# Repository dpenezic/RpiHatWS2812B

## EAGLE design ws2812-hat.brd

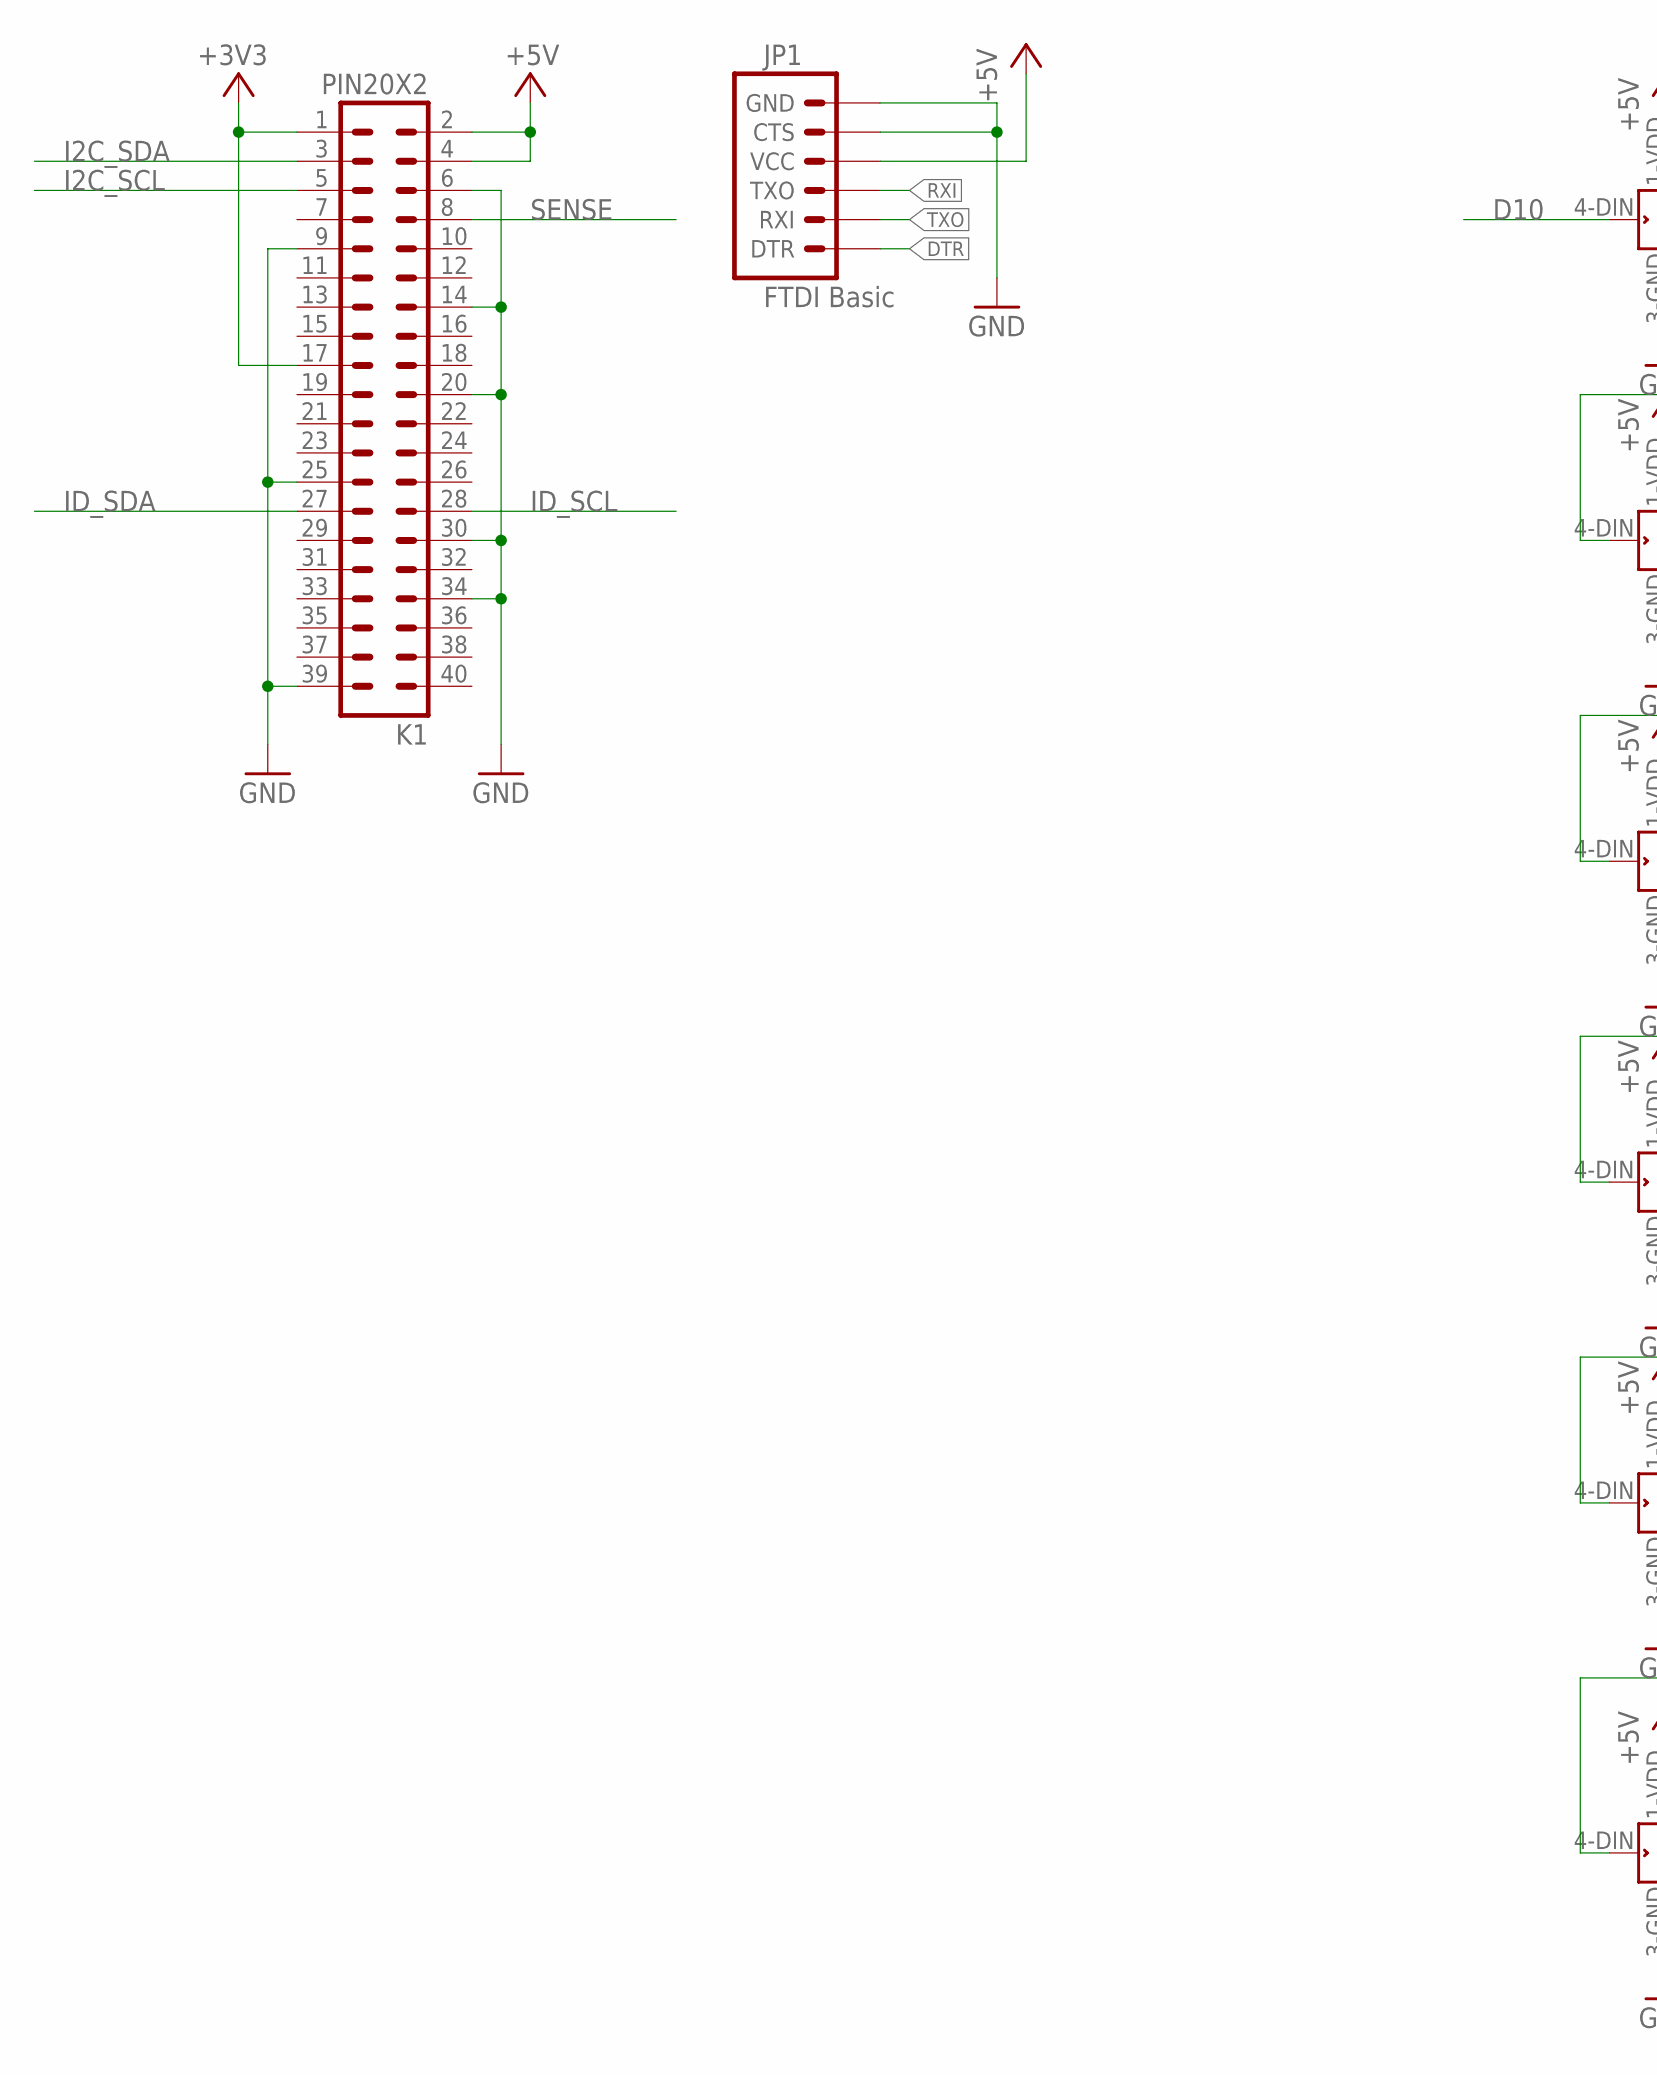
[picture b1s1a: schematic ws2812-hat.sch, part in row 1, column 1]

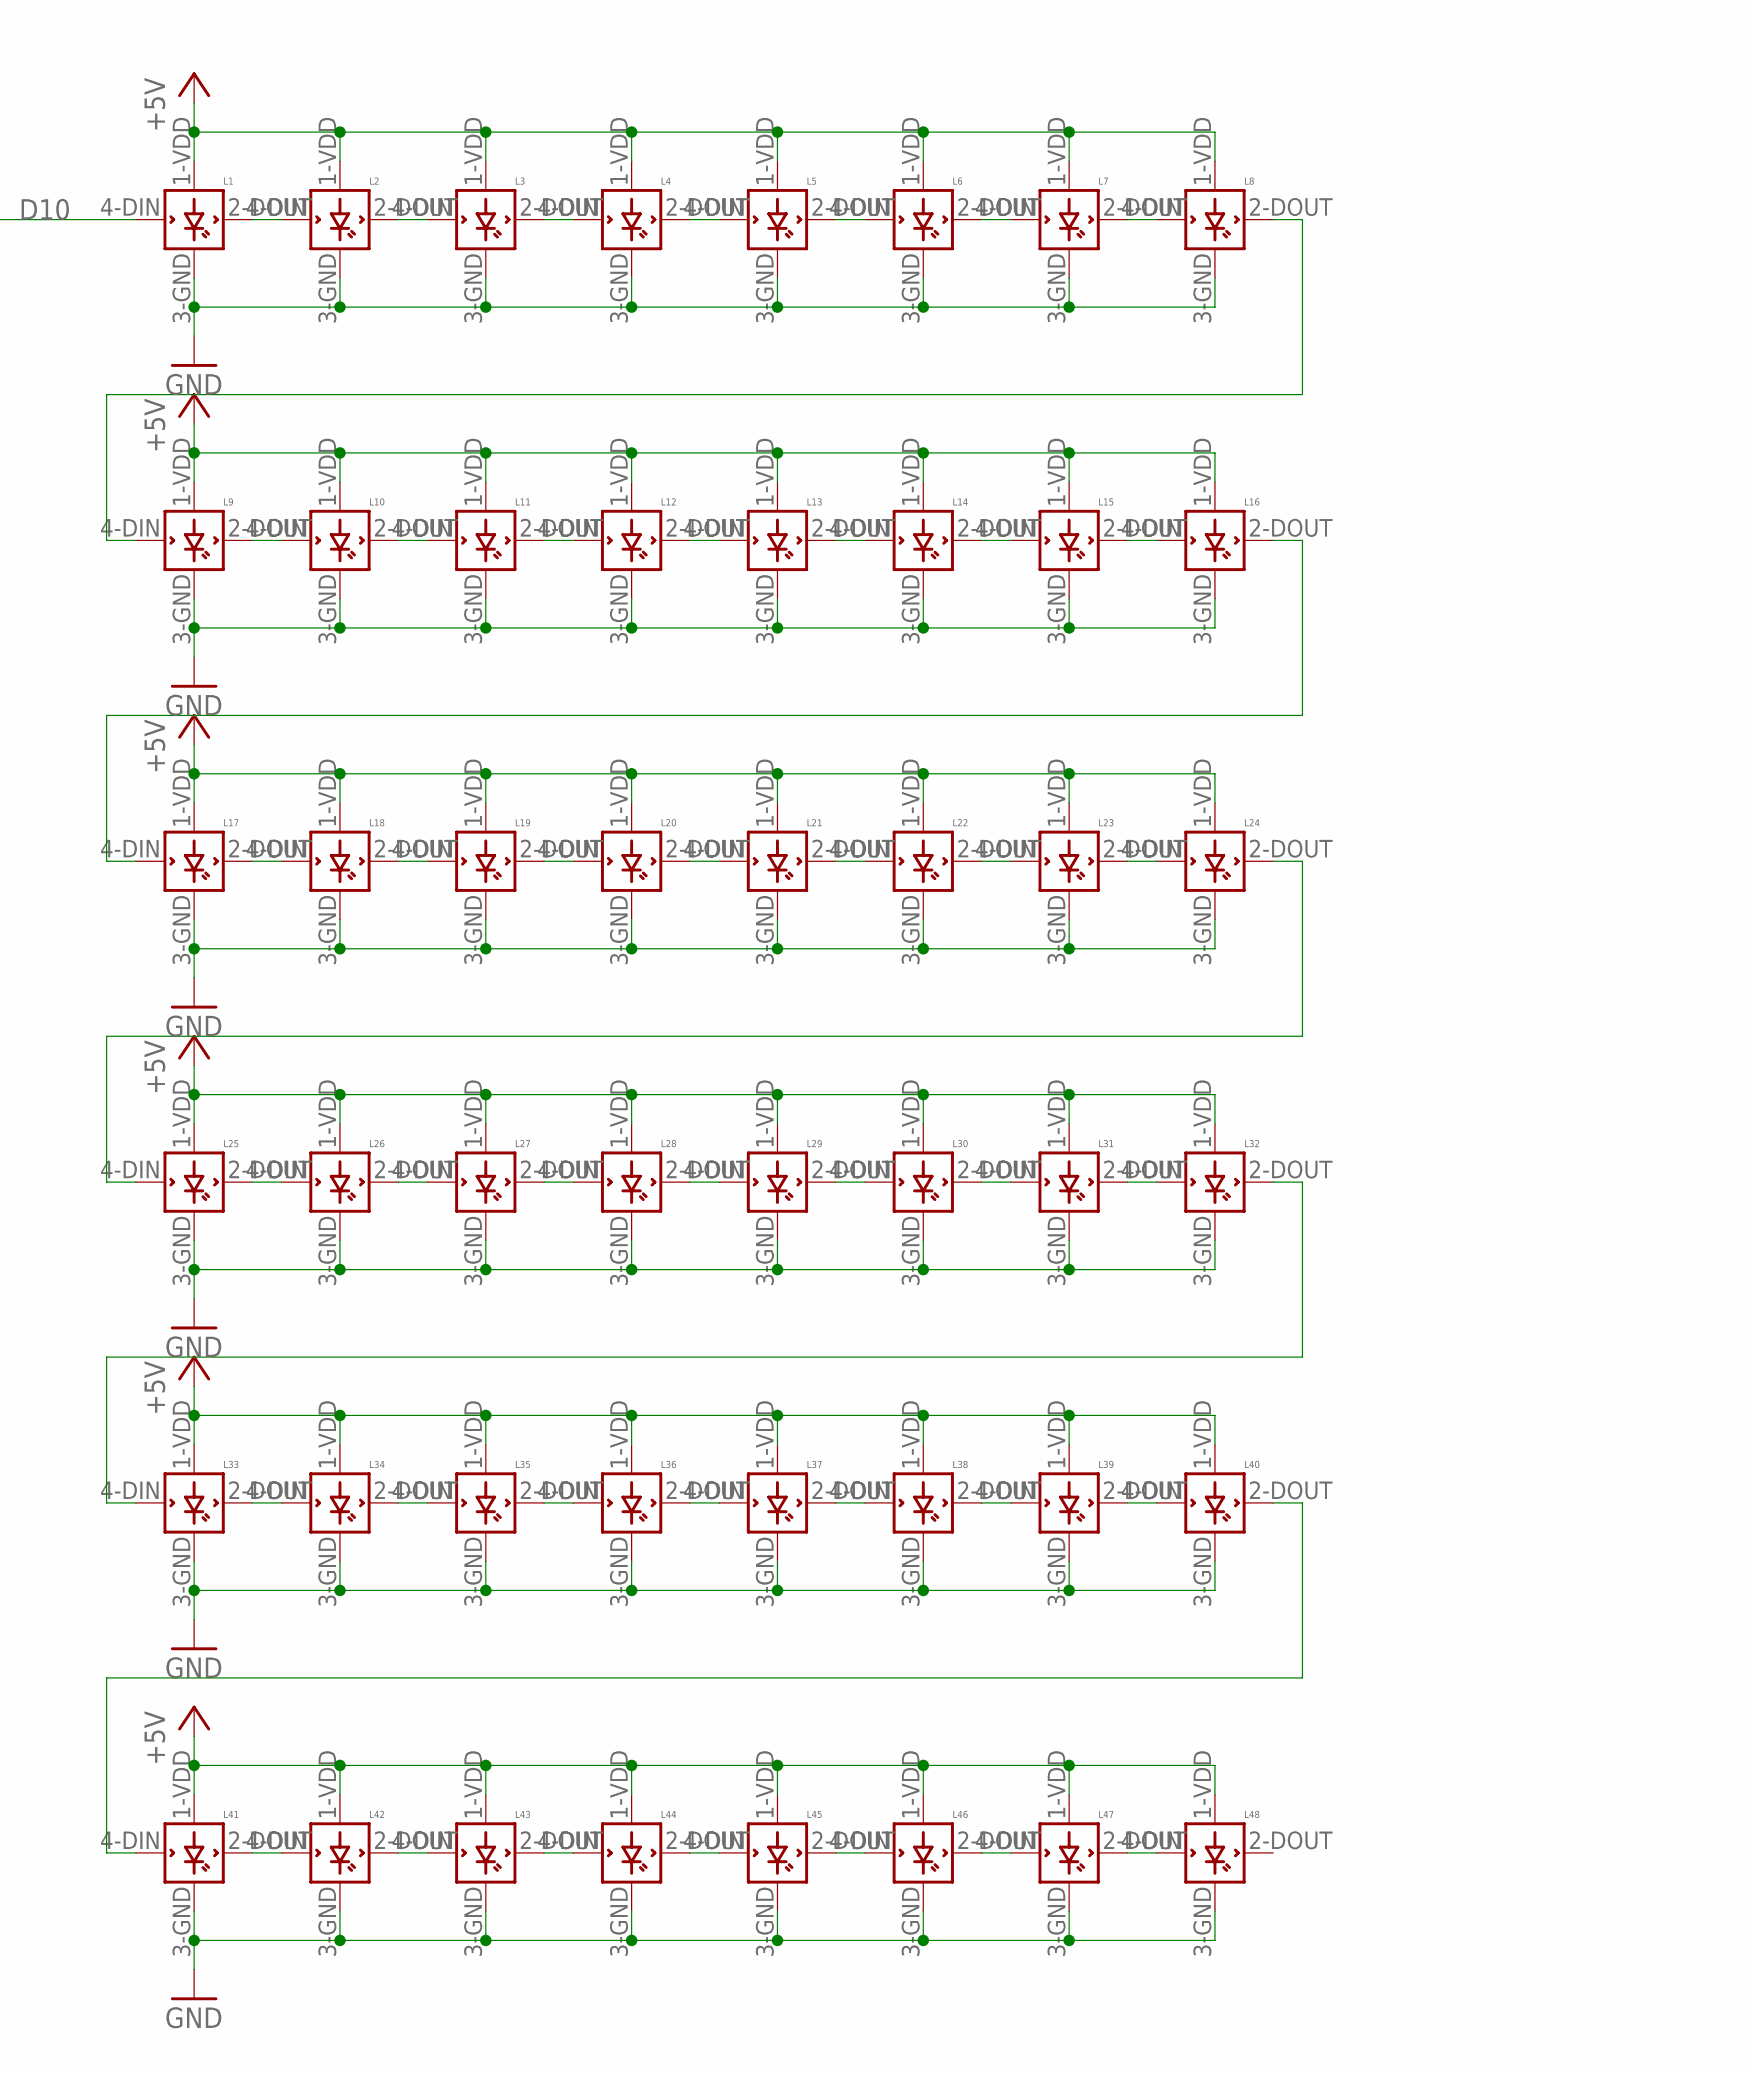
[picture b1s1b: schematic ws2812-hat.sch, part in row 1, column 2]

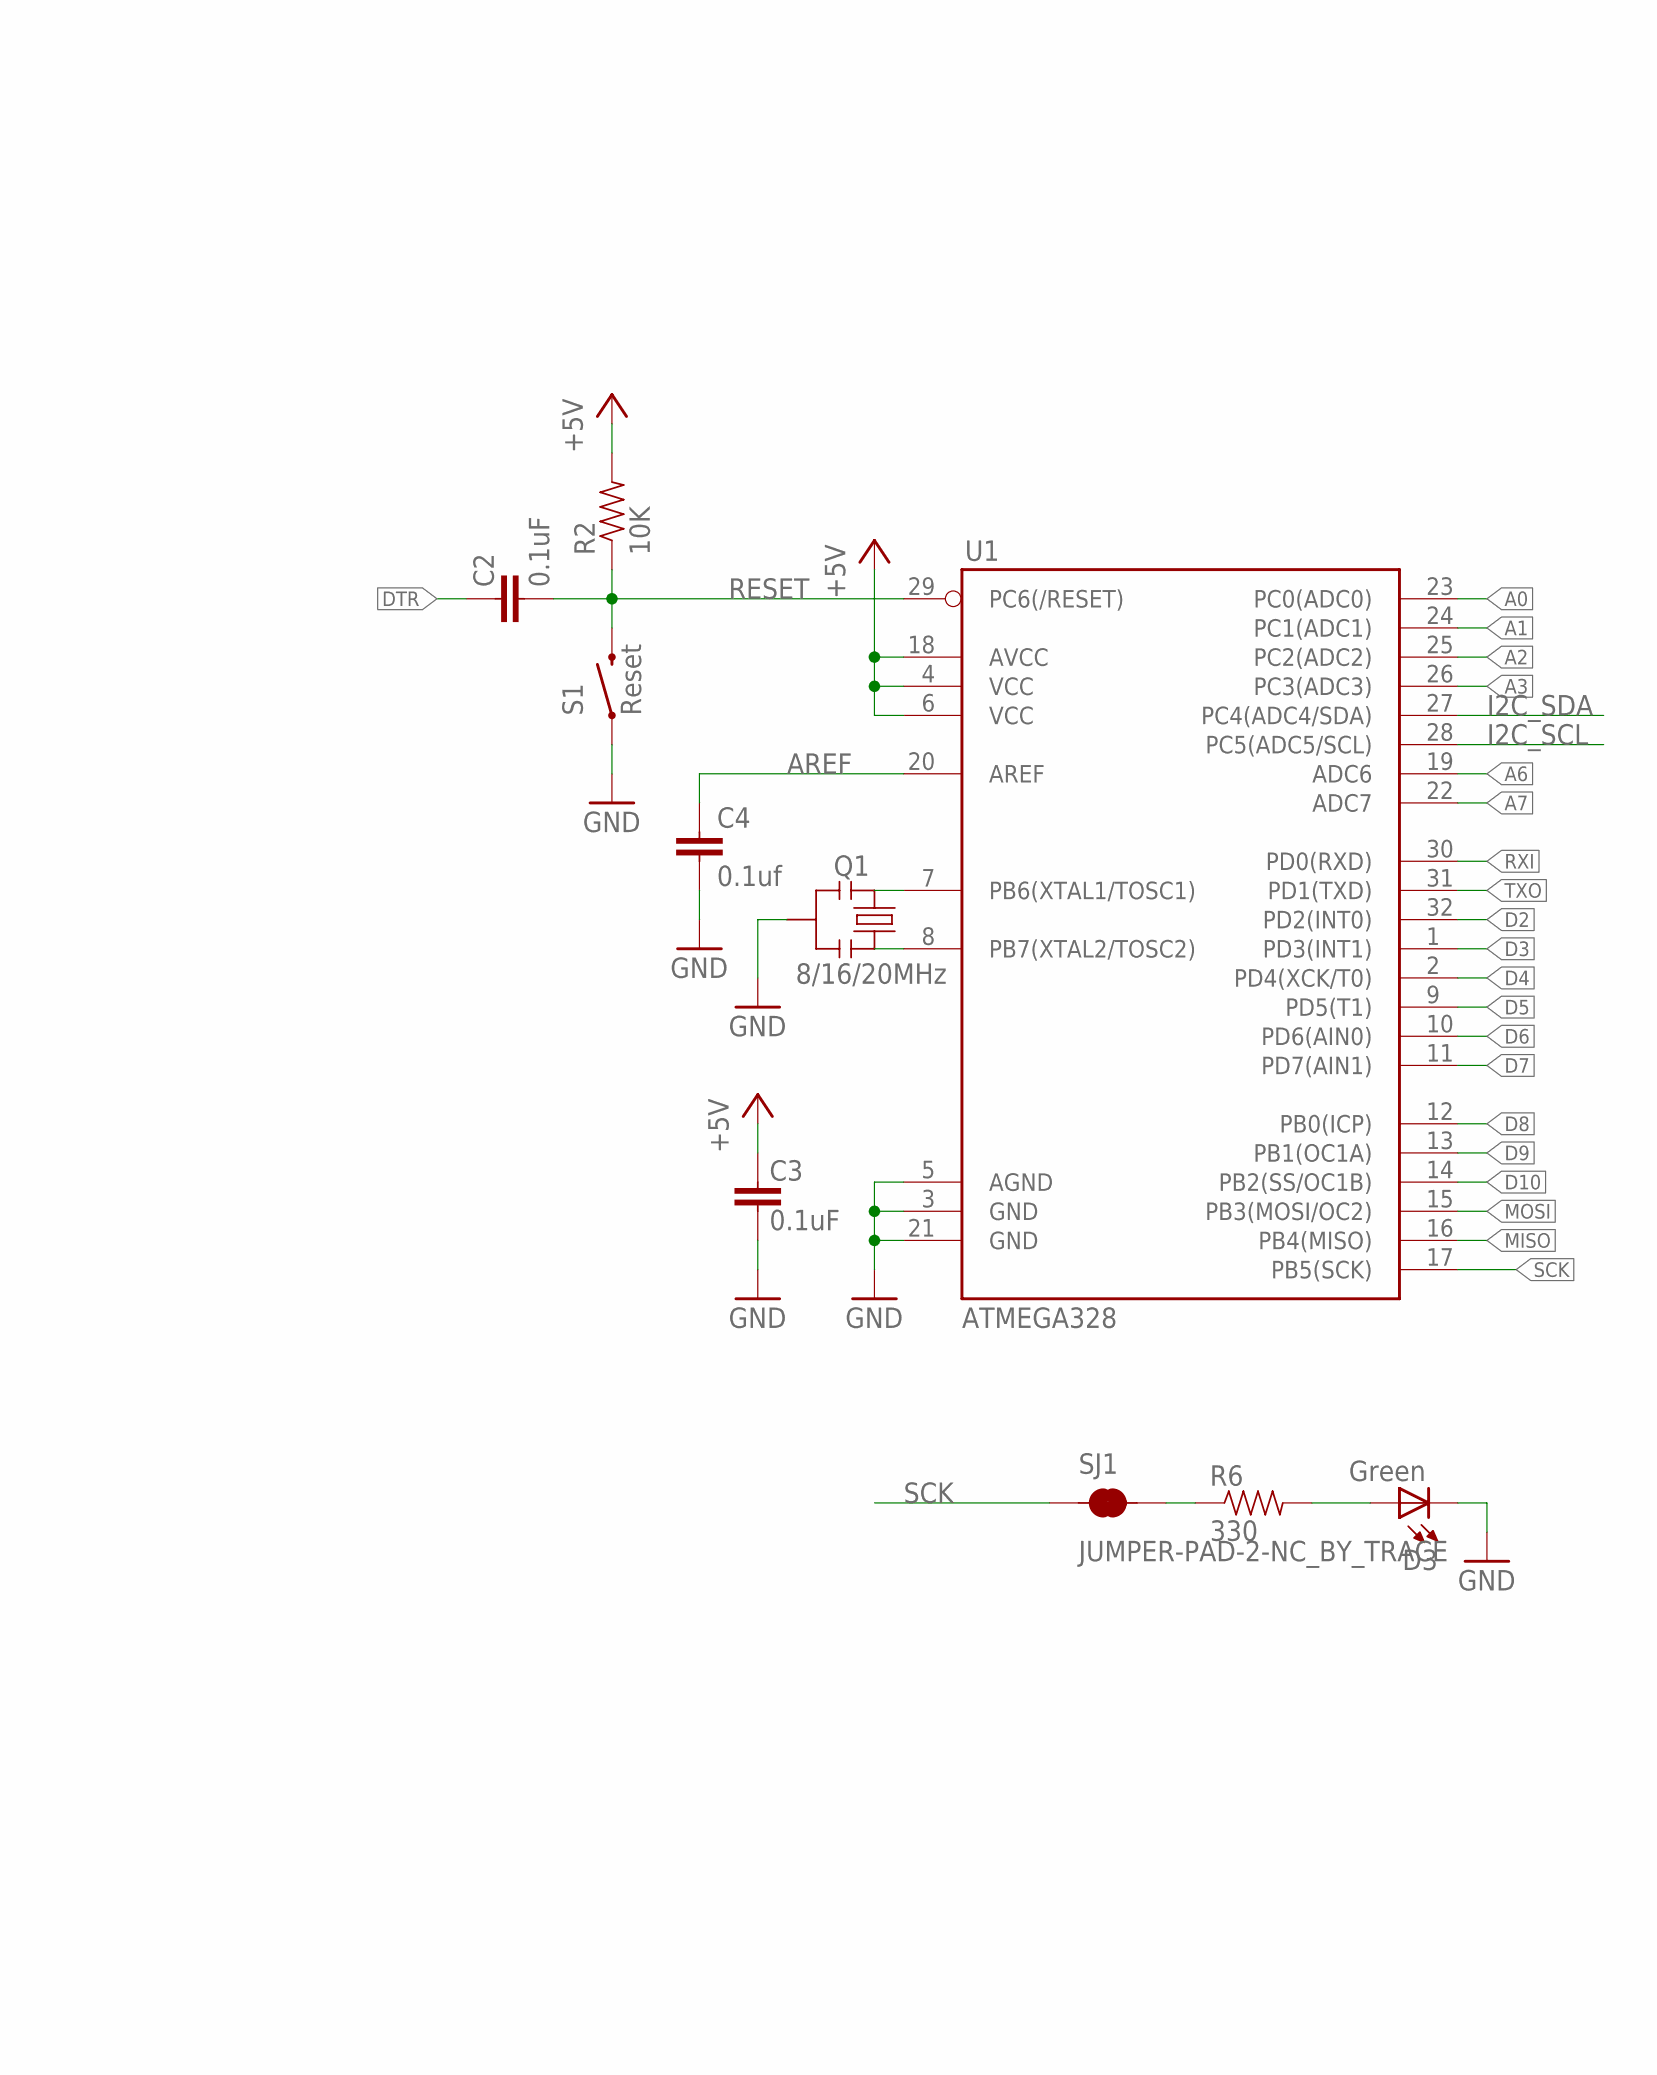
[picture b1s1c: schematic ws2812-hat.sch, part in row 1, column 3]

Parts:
C2, C3: 0.1uF; 0603-CAP
C4: 0.1uf; C0805K
D3: Green; 0603-LED-ALT1
JP1: FTDI Basic; 1X06
K1: PIN20X2; PIN_20X2
L1, L2, L3, L4, L5, L6, L7, L8, L9, L10, L11, L12, L13, L14, L15, L16, L17, L18, L19, L20, L21, L22, L23, L24, L25, L26, L27, L28, L29, L30, L31, L32, L33, L34, L35, L36, L37, L38, L39, L40, L41, L42, L43, L44, L45, L46, L47, L48: WS2812B
Q1: 8/16/20MHz; RESONATOR-SMD-1:1
R2: 10K; 0603-RES
R6: 330; 0603-RES
S1: Reset; TACTILE-SWITCH-SMD-ALT01
SJ1: JUMPER-PAD-2-NC_BY_TRACE; PAD-JUMPER-2-NC_BY_TRACE_YES_SILK
U1: ATMEGA328; TQFP32-08

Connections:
+3V3: K1.1, K1.17
+5V: C3.2, JP1.4 (VCC), K1.2, K1.4, L1.1-VDD (VDD), L2.1-VDD (VDD), L3.1-VDD (VDD), L4.1-VDD (VDD), L5.1-VDD (VDD), L6.1-VDD (VDD), L7.1-VDD (VDD), L8.1-VDD (VDD), L9.1-VDD (VDD), L10.1-VDD (VDD), L11.1-VDD (VDD), L12.1-VDD (VDD), L13.1-VDD (VDD), L14.1-VDD (VDD), L15.1-VDD (VDD), L16.1-VDD (VDD), L17.1-VDD (VDD), L18.1-VDD (VDD), L19.1-VDD (VDD), L20.1-VDD (VDD), L21.1-VDD (VDD), L22.1-VDD (VDD), L23.1-VDD (VDD), L24.1-VDD (VDD), L25.1-VDD (VDD), L26.1-VDD (VDD), L27.1-VDD (VDD), L28.1-VDD (VDD), L29.1-VDD (VDD), L30.1-VDD (VDD), L31.1-VDD (VDD), L32.1-VDD (VDD), L33.1-VDD (VDD), L34.1-VDD (VDD), L35.1-VDD (VDD), L36.1-VDD (VDD), L37.1-VDD (VDD), L38.1-VDD (VDD), L39.1-VDD (VDD), L40.1-VDD (VDD), L41.1-VDD (VDD), L42.1-VDD (VDD), L43.1-VDD (VDD), L44.1-VDD (VDD), L45.1-VDD (VDD), L46.1-VDD (VDD), L47.1-VDD (VDD), L48.1-VDD (VDD), R2.2, U1.4 (VCC), U1.6 (VCC), U1.18 (AVCC)
A0: U1.23 (PC0(ADC0))
A1: U1.24 (PC1(ADC1))
A2: U1.25 (PC2(ADC2))
A3: U1.26 (PC3(ADC3))
A6: U1.19 (ADC6)
A7: U1.22 (ADC7)
AREF: C4.1, U1.20 (AREF)
D2: U1.32 (PD2(INT0))
D3: U1.1 (PD3(INT1))
D4: U1.2 (PD4(XCK/T0))
D5: U1.9 (PD5(T1))
D6: U1.10 (PD6(AIN0))
D7: U1.11 (PD7(AIN1))
D8: U1.12 (PB0(ICP))
D9: U1.13 (PB1(OC1A))
D10: L1.4-DIN (DIN), U1.14 (PB2(SS/OC1B))
DTR: C2.2, JP1.1 (DTR)
GND: C3.1, C4.2, D3.C, JP1.5 (CTS), JP1.6 (GND), K1.6, K1.9, K1.14, K1.20, K1.25, K1.30, K1.34, K1.39, L1.3-GND (GND), L2.3-GND (GND), L3.3-GND (GND), L4.3-GND (GND), L5.3-GND (GND), L6.3-GND (GND), L7.3-GND (GND), L8.3-GND (GND), L9.3-GND (GND), L10.3-GND (GND), L11.3-GND (GND), L12.3-GND (GND), L13.3-GND (GND), L14.3-GND (GND), L15.3-GND (GND), L16.3-GND (GND), L17.3-GND (GND), L18.3-GND (GND), L19.3-GND (GND), L20.3-GND (GND), L21.3-GND (GND), L22.3-GND (GND), L23.3-GND (GND), L24.3-GND (GND), L25.3-GND (GND), L26.3-GND (GND), L27.3-GND (GND), L28.3-GND (GND), L29.3-GND (GND), L30.3-GND (GND), L31.3-GND (GND), L32.3-GND (GND), L33.3-GND (GND), L34.3-GND (GND), L35.3-GND (GND), L36.3-GND (GND), L37.3-GND (GND), L38.3-GND (GND), L39.3-GND (GND), L40.3-GND (GND), L41.3-GND (GND), L42.3-GND (GND), L43.3-GND (GND), L44.3-GND (GND), L45.3-GND (GND), L46.3-GND (GND), L47.3-GND (GND), L48.3-GND (GND), Q1.2, S1.1, S1.2 (1), U1.3 (GND), U1.5 (AGND), U1.21 (GND)
I2C_SCL: K1.5, U1.28 (PC5(ADC5/SCL))
I2C_SDA: K1.3, U1.27 (PC4(ADC4/SDA))
ID_SCL: K1.28
ID_SDA: K1.27
MISO: U1.16 (PB4(MISO))
MOSI: U1.15 (PB3(MOSI/OC2))
unnamed: L9.2-DOUT (DOUT), L10.4-DIN (DIN)
unnamed: L1.2-DOUT (DOUT), L2.4-DIN (DIN)
unnamed: L2.2-DOUT (DOUT), L3.4-DIN (DIN)
unnamed: L3.2-DOUT (DOUT), L4.4-DIN (DIN)
unnamed: L4.2-DOUT (DOUT), L5.4-DIN (DIN)
unnamed: L5.2-DOUT (DOUT), L6.4-DIN (DIN)
unnamed: L6.2-DOUT (DOUT), L7.4-DIN (DIN)
unnamed: L7.2-DOUT (DOUT), L8.4-DIN (DIN)
unnamed: L10.2-DOUT (DOUT), L11.4-DIN (DIN)
unnamed: L11.2-DOUT (DOUT), L12.4-DIN (DIN)
unnamed: L12.2-DOUT (DOUT), L13.4-DIN (DIN)
unnamed: L13.2-DOUT (DOUT), L14.4-DIN (DIN)
unnamed: L14.2-DOUT (DOUT), L15.4-DIN (DIN)
unnamed: L15.2-DOUT (DOUT), L16.4-DIN (DIN)
unnamed: L17.2-DOUT (DOUT), L18.4-DIN (DIN)
unnamed: L18.2-DOUT (DOUT), L19.4-DIN (DIN)
unnamed: L19.2-DOUT (DOUT), L20.4-DIN (DIN)
unnamed: L20.2-DOUT (DOUT), L21.4-DIN (DIN)
unnamed: L21.2-DOUT (DOUT), L22.4-DIN (DIN)
unnamed: L22.2-DOUT (DOUT), L23.4-DIN (DIN)
unnamed: L23.2-DOUT (DOUT), L24.4-DIN (DIN)
unnamed: L25.2-DOUT (DOUT), L26.4-DIN (DIN)
unnamed: L26.2-DOUT (DOUT), L27.4-DIN (DIN)
unnamed: L27.2-DOUT (DOUT), L28.4-DIN (DIN)
unnamed: L28.2-DOUT (DOUT), L29.4-DIN (DIN)
unnamed: L29.2-DOUT (DOUT), L30.4-DIN (DIN)
unnamed: L30.2-DOUT (DOUT), L31.4-DIN (DIN)
unnamed: L31.2-DOUT (DOUT), L32.4-DIN (DIN)
unnamed: D3.A, R6.2
unnamed: Q1.3, U1.8 (PB7(XTAL2/TOSC2))
unnamed: Q1.1, U1.7 (PB6(XTAL1/TOSC1))
unnamed: L33.2-DOUT (DOUT), L34.4-DIN (DIN)
unnamed: L34.2-DOUT (DOUT), L35.4-DIN (DIN)
unnamed: L35.2-DOUT (DOUT), L36.4-DIN (DIN)
unnamed: L36.2-DOUT (DOUT), L37.4-DIN (DIN)
unnamed: L37.2-DOUT (DOUT), L38.4-DIN (DIN)
unnamed: L38.2-DOUT (DOUT), L39.4-DIN (DIN)
unnamed: L39.2-DOUT (DOUT), L40.4-DIN (DIN)
unnamed: L41.2-DOUT (DOUT), L42.4-DIN (DIN)
unnamed: L42.2-DOUT (DOUT), L43.4-DIN (DIN)
unnamed: L43.2-DOUT (DOUT), L44.4-DIN (DIN)
unnamed: L44.2-DOUT (DOUT), L45.4-DIN (DIN)
unnamed: L45.2-DOUT (DOUT), L46.4-DIN (DIN)
unnamed: L46.2-DOUT (DOUT), L47.4-DIN (DIN)
unnamed: L47.2-DOUT (DOUT), L48.4-DIN (DIN)
unnamed: L8.2-DOUT (DOUT), L9.4-DIN (DIN)
unnamed: L16.2-DOUT (DOUT), L17.4-DIN (DIN)
unnamed: L24.2-DOUT (DOUT), L25.4-DIN (DIN)
unnamed: L40.2-DOUT (DOUT), L41.4-DIN (DIN)
unnamed: L32.2-DOUT (DOUT), L33.4-DIN (DIN)
unnamed: R6.1, SJ1.2
RESET: C2.1, R2.1, S1.3 (2), S1.4 (2), U1.29 (PC6(/RESET))
RXI: JP1.3 (TXO), U1.30 (PD0(RXD))
SCK: SJ1.1, U1.17 (PB5(SCK))
SENSE: K1.8
TXO: JP1.2 (RXI), U1.31 (PD1(TXD))

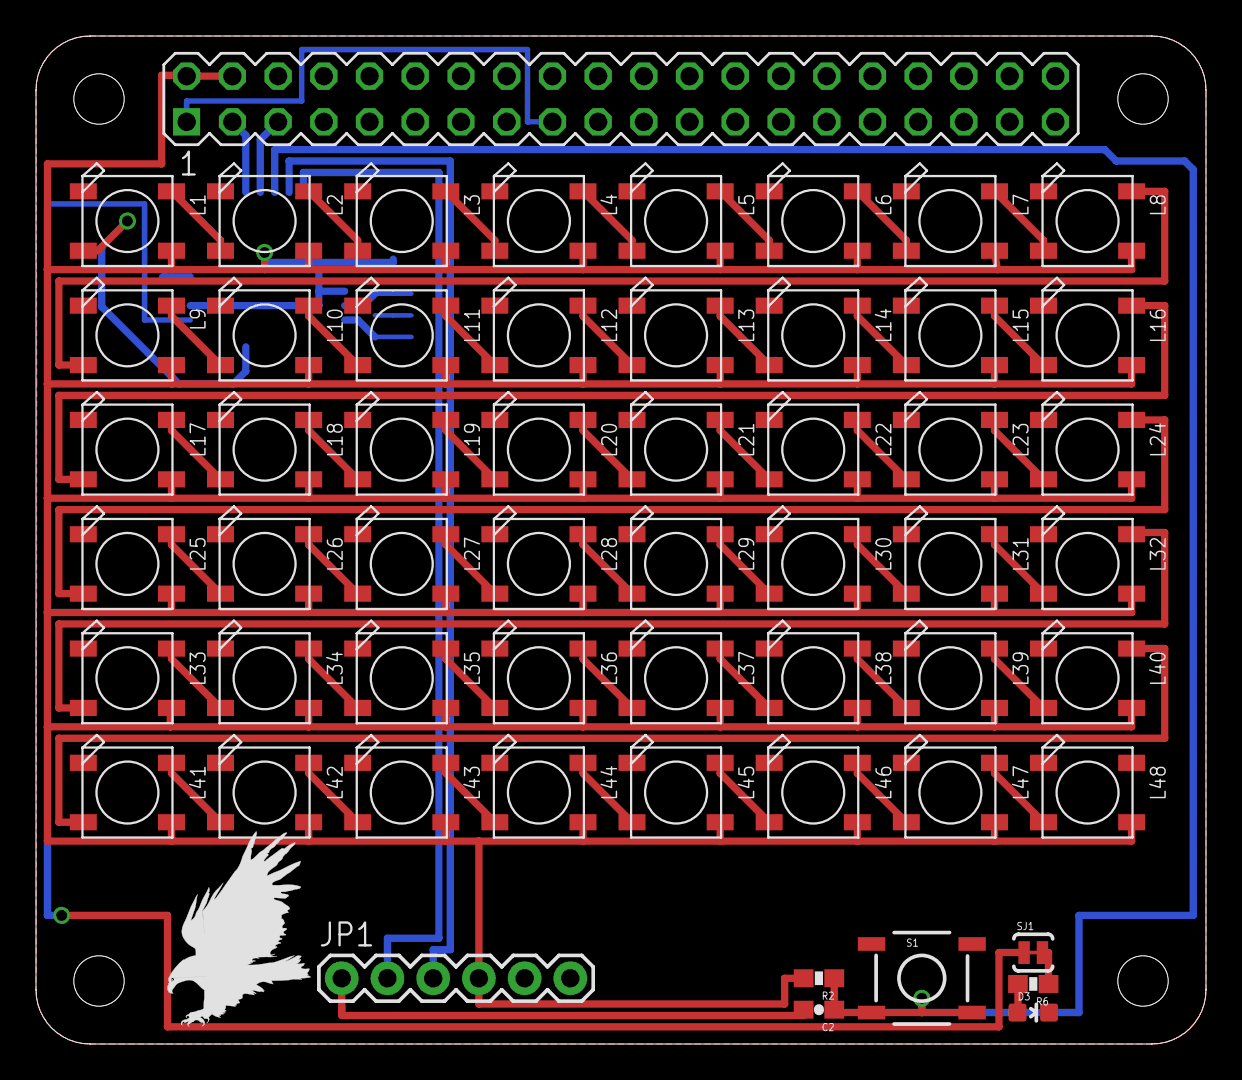
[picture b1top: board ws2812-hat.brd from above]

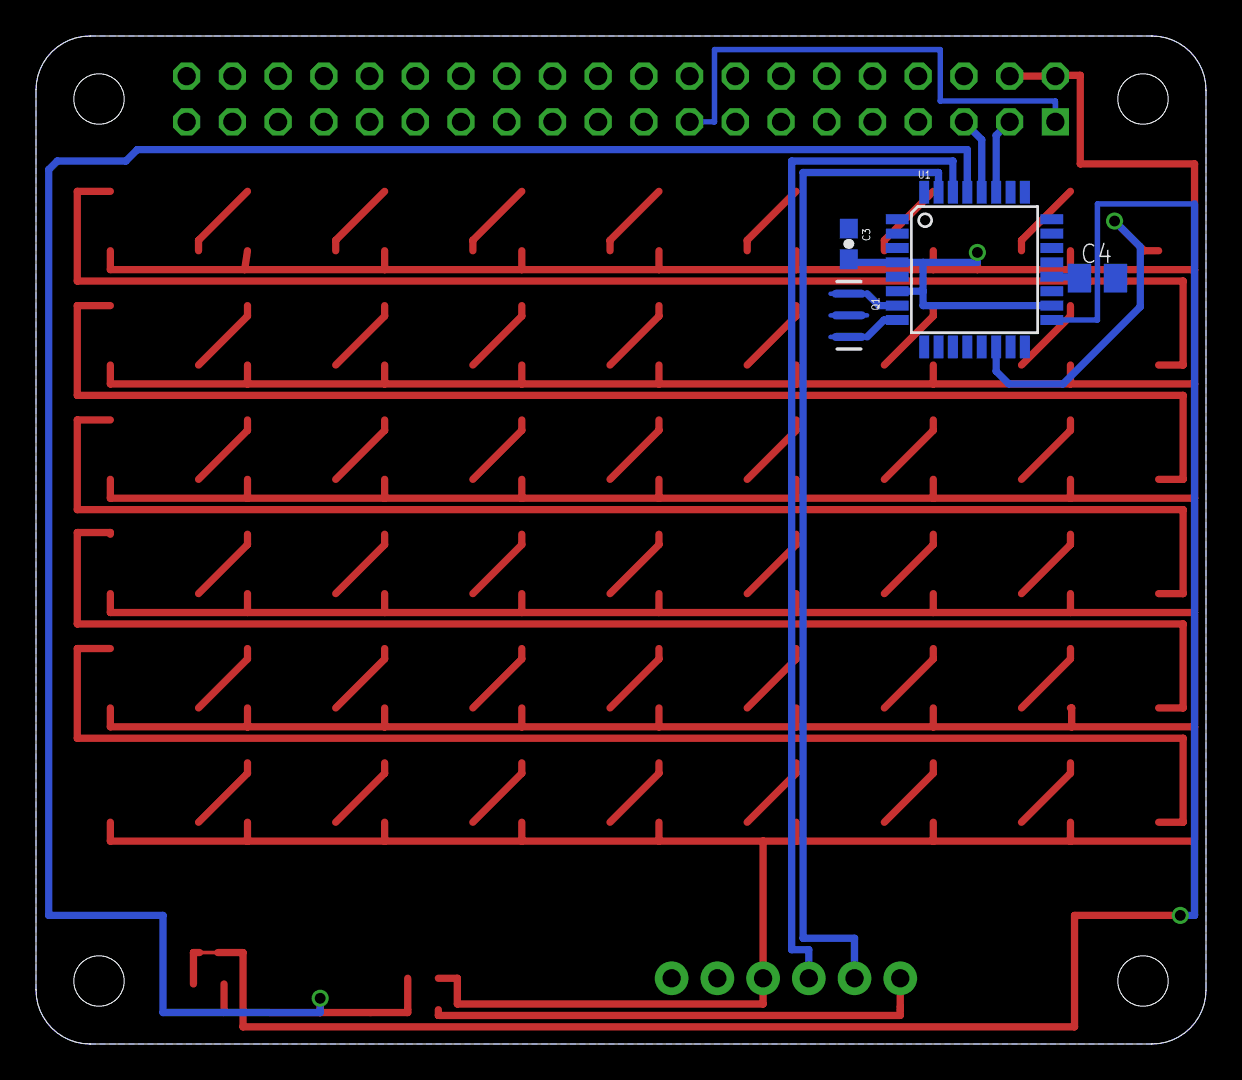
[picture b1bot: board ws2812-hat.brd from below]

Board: 2 copper layers, 65.0 x 56.0 mm, 61 parts (4 on the bottom side), 63 nets.

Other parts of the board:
U$1: EAGLE-PLC-8MM

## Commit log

2015-03-03 Adafruit lib
2015-03-03 WS2812B board
2015-03-03 Renamed
2015-03-03 More finished-er
2015-03-03 Add board graphic
2015-03-03 Add board graphic... BUT BIGGER

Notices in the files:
parts and their libraries:
SparkFun-Passives: Licensing: Creative Commons ShareAlike 4.0 International - https://creativecommons.org/licenses/by-sa/4.0
